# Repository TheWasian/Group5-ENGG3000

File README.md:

<div align="center">

# Whack-A-Mole · Wacker5

**Turn movement into gameplay with ultrasonic tracking and a 3D browser game.**

Three ESP32 boards. Six targets. One interactive engineering project.

[Overview](#overview) · [Gallery](#gallery) · [Getting started](#getting-started) · [Hardware](#hardware) · [Development](#development) · [Documentation](#documentation)

</div>

## Overview

Wacker5 brings a physical control system to the classic Whack-A-Mole game. Three ESP32-S3 boards use ultrasonic sensors to estimate a player's position, then send tracking data to a browser game where movement controls the hammer across six mole targets. You can also play with a mouse without connecting the hardware.

Built by **Group 5 for ENGG3000**, the project brings together embedded firmware, browser graphics, custom electronics, enclosure design, and sensor calibration. This repository contains the game, firmware, KiCad PCB designs, CAD models, and development records.

### Highlights

- **3D gameplay:** animated moles, a six-hole board, and five environments rendered with Three.js.
- **Arcade mechanics:** normal, golden, freeze, and bomb moles, with scores, lives, levels, and hit streaks.
- **Physical interaction:** three ultrasonic sensors track movement using two- or three-sensor position estimates.
- **Filtered tracking:** spike rejection and position smoothing; stale or held positions cannot score hits.
- **Live diagnostics:** the ESP32 hosts a dashboard showing sensor coverage, tracking, and target positions.
- **Local operation:** the game ships with its graphics bundle, and the hardware creates its own Wi-Fi network.
- **Hardware design files:** PCB schematics, board layouts, fabrication files, and printable enclosure models.

## Gallery

<table>
  <tr>
    <th>Physical prototype</th>
    <th>Current game interface</th>
  </tr>
  <tr>
    <td align="center"></td>
    <td align="center"></td>
  </tr>
</table>

The prototype photo shows the physical tracking setup. The current game screenshot shows the Sunny Garden environment, with 3D moles, six targets, and the score, lives, and hit-streak displays.

<details>
<summary><strong>View the custom PCB layout</strong></summary>

The PCB design and fabrication resources are in [ENGG3000-BaseStation](ENGG3000-BaseStation/).

</details>

## How it works

```mermaid
flowchart LR
    L[Left ultrasonic sensor] --> N1[ESP32 sensor node 1]
    C[Centre ultrasonic sensor] --> AP[ESP32 access point]
    R[Right ultrasonic sensor] --> N2[ESP32 sensor node 2]
    N1 <-->|ESP-NOW| AP
    N2 <-->|ESP-NOW| AP
    AP --> P[Position estimation and filtering]
    P --> API[Local HTTP API]
    API --> G[Browser game]
    API --> D[Live tracking dashboard]
```

The centre board coordinates range measurements and combines the readings into a position estimate. The browser maps valid, fresh positions into the game area and checks hits. When tracking briefly drops out, the last position may remain visible, but it cannot earn points.

The dashboard is hosted on the ESP32 at [192.168.4.1](http://192.168.4.1/). The game itself runs from the `UI-Code` folder on your computer.

## Getting started

### Play without hardware

1. Clone or download this repository. Extract the ZIP if downloading it.
2. Open `UI-Code/index.html` in a browser.
3. Select **Start Game**, then click the moles as they appear.

Keep the entire `UI-Code` folder together. The bundled game does not need Node.js, npm, or a development server to play. A WebGL 2 capable browser enables the 3D graphics; a CSS fallback is available if the renderer cannot start. Sound starts muted and can be enabled with the sound button.

### Play with the sensor system

1. Wire and upload the three board sketches using the [hardware setup guide](ESP-32%20Code/CHECKLIST.md).
2. Power the centre access point, followed by the left and right sensor nodes.
3. Connect your computer to **Wacker5** using the connection details in the setup guide.
4. Open the [tracking dashboard](http://192.168.4.1/) and confirm both nodes are online.
5. Open `UI-Code/index.html`, start the game, and move between the configured physical targets.

On Windows, you can run [GameLauncher.bat](GameLauncher.bat) to connect to Wacker5 and open the game. The launcher uses [Connect-Wacker5.ps1](Connect-Wacker5.ps1) to manage the Wi-Fi connection.

Keep the computer connected to Wacker5 while playing with sensors, and allow browser requests to the local controller if prompted. Sensor spacing, aiming, and target calibration are covered in the setup guide.

### Sensor cone visualisation and calibration

The [cones.html dashboard](ESP-32%20Code/Access_Point/cones.html) provides a live top-down view of the sensor setup. While connected to **Wacker5**, open [http://192.168.4.1/cones](http://192.168.4.1/cones) (the same dashboard is available at the controller's root address). The page is embedded in the access-point firmware, so there is no separate dashboard server to start.

- **Visualise coverage:** see each sensor's configured cone, overlapping coverage, measured echo arcs, player position, and the six game targets. Switch between the playing-area view and full sensor range to inspect alignment.
- **Check the setup:** use the live distances, sensor status, and aim angles to compare the physical layout with the firmware settings. The **Where to stand** table gives target positions in centimetres.
- **Try floor-position calibration:** stand at a chosen spot, select **Calibrate hole N**, and stay still through the countdown and capture. Repeat for the six holes, then walk between them to test detection with a 10, 15, or 20 cm test radius.

**Calibration on this page is a browser-only preview.** Saved positions stay in that browser's local storage; they do not change the ESP32 configuration or the game's hit zones. The cones represent the configured beam model, not measured detection boundaries. Recheck the physical setup and recalibrate after moving sensors. See the [calibration workflow](ESP-32%20Code/CHECKLIST.md#cone-page-hole-calibration-experiment) for details.

## Hardware

The tracking system uses **three ESP32-S3 boards with one ultrasonic sensor per board**.

The current layout has **30 cm between adjacent sensor references** (60 cm across the outer pair), with the centre sensor facing straight ahead and the side sensors angled **15.9° inward**. The [physical placement guide](ESP-32%20Code/CHECKLIST.md#physical-placement-spacing-and-angles) explains the reference points, screen distance, and housing setback.

| Component | Role | Firmware |
| --- | --- | --- |
| Centre ESP32-S3 + sensor | Wi-Fi access point, tracking, dashboard, and game API | [Access_Point](ESP-32%20Code/Access_Point/) |
| Left ESP32-S3 + sensor | Left-side range measurements | [Sensor_Node_1](ESP-32%20Code/Sensor_Node_1/) |
| Right ESP32-S3 + sensor | Right-side range measurements | [Sensor_Node_2](ESP-32%20Code/Sensor_Node_2/) |
| Computer with a browser | Game display and player interface | [UI-Code](UI-Code/) |
| Custom PCB and enclosures | Electronics integration and sensor mounting | [PCB files](ENGG3000-BaseStation/) · [CAD files](CAD/) |

Use the [setup guide](ESP-32%20Code/CHECKLIST.md) for pin assignments, sensor electrical requirements, firmware uploads, and physical alignment. The [bill of materials](Bill_of_materials.md) records the project's initial component cost estimate.

## Development

### Serve the game locally

For browser fixtures and development, run this from the repository root with Python 3:

```sh
python -m http.server 8000 --bind 127.0.0.1
```

Open the [game](http://127.0.0.1:8000/UI-Code/) or the [3D model gallery](http://127.0.0.1:8000/UI-Code/tests/three-preview.html). On systems where Python 3 is named `python3`, use that command instead.

### Build and check the game

With Node.js and npm installed:

```sh
cd UI-Code
npm ci
npm run build
npm run check:bundle
npm test
```

Rebuild after editing the 3D modules or vendored Three.js sources, and include the regenerated bundle with your changes. The checks cover models, bundle consistency, sound, and rendering performance logic. See the [3D development guide](UI-Code/3D-README.md) for browser previews and sensor-hit fixtures.

### Check tracking and backend logic

Run these from the repository root. The native suite needs Bash and a C++ compiler with AddressSanitizer and UndefinedBehaviorSanitizer support, such as a suitable Linux or WSL environment.

```sh
bash "ESP-32 Code/tests/run_native.sh"
node "ESP-32 Code/tests/game_backend_test.cjs"
node "ESP-32 Code/tests/hole_calibration_test.cjs"
```

Software checks complement physical testing: sensor accuracy and coverage must also be verified with the assembled hardware.

## Repository structure

| Path | Contents |
| --- | --- |
| [UI-Code/](UI-Code/) | Browser game, game services, 3D rendering, and frontend tests |
| [ESP-32 Code/](ESP-32%20Code/) | Access point and sensor firmware, tracking logic, dashboard, and tests |
| [ESP-32 Code/calibration/](ESP-32%20Code/calibration/) | Data-logging firmware, Python capture tools, and calibration results |
| [ENGG3000-BaseStation/](ENGG3000-BaseStation/) | KiCad project, component libraries, and fabrication outputs |
| [CAD/](CAD/) | Enclosure and hardware models in STL and GLB formats |
| [Blender/](Blender/) | Blender demonstration scene files |
| [WeeklyLogs/](WeeklyLogs/) | Sprint notes, progress screenshots, and testing records |

## Documentation

- [Hardware setup and troubleshooting](ESP-32%20Code/CHECKLIST.md)
- [3D game architecture and development](UI-Code/3D-README.md)
- [Sensor calibration and data collection](ESP-32%20Code/calibration/README.md)
- [Bill of materials](Bill_of_materials.md)
- [Project development logs](WeeklyLogs/)

## Contributing

Issues and pull requests are welcome. Describe the behaviour you want to change, include steps to reproduce bugs, and run the checks relevant to your changes. For hardware or tracking changes, include the board configuration, sensor arrangement, and physical test results where available.

## Team

Developed by ENGG3000 Group 5: **Alleluya Hamisi, Matthew Thompson, Fouad Ayoub, Cammilus John Baptist, and Shreenidhi Arunachalam**.

## License

This project is available under the [MIT License](LICENSE). Vendored Three.js retains its own [MIT license](UI-Code/vendor/three/LICENSE).

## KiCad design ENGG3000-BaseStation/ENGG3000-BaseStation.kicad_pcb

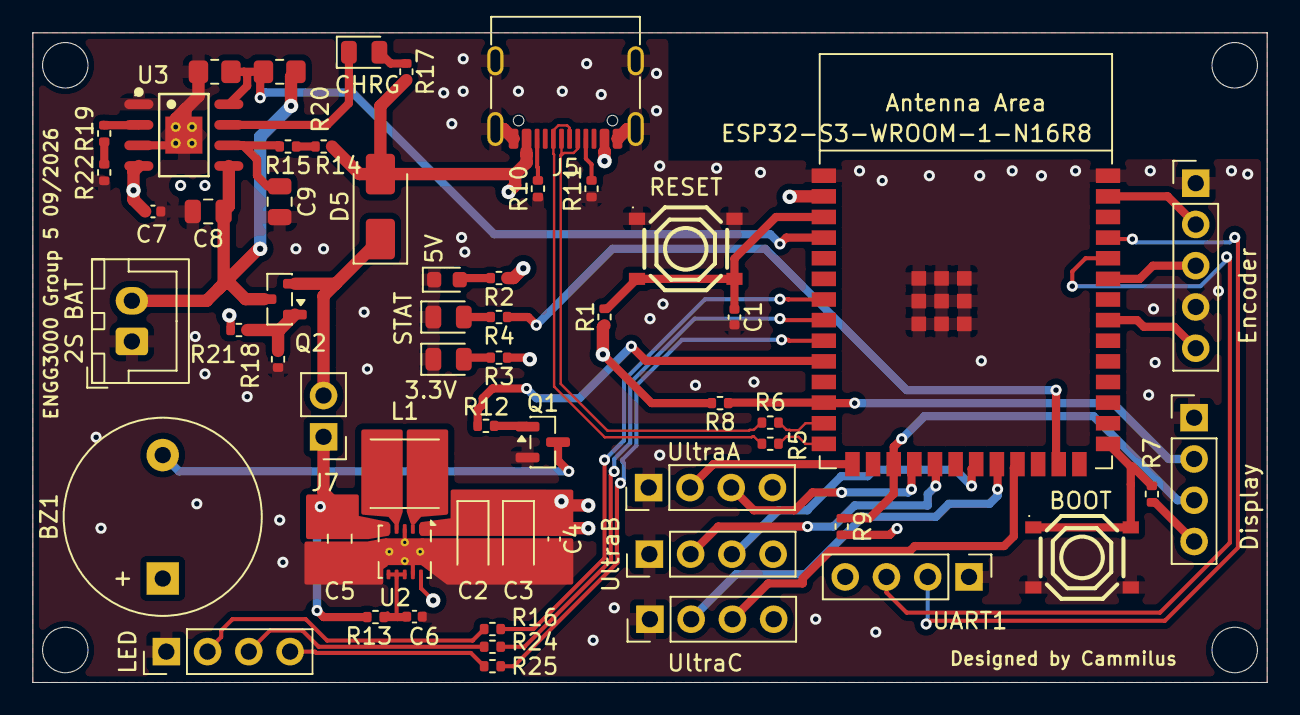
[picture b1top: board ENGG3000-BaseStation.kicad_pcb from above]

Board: 4 copper layers, 76.0 x 40.0 mm, 58 parts (0 on the bottom side), 51 nets.

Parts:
2S BAT: NiMH 2S Pack; JST_XH_B2B-XH-A_1x02_P2.50mm_Vertical
3.3V: 3.3V; LED_0805_2012Metric
5V: 5V; LED_0603_1608Metric
BOOT: BOOT; SW-SMD_4P-L5.1-W5.1-P3.70-LS6.5-TL_H1.5
BZ1: Buzzer; Buzzer_12x9.5RM7.6
C1, C4, C7: 1uF; C_0402_1005Metric
C2, C3: 10uF; CP_EIA-3216-18_Kemet-A
C5, C8, C9: 10uF; C_0805_2012Metric
C6: 100nF; C_0402_1005Metric
CHRG: CHRG; LED_0805_2012Metric
D5: SS14; D_SMA
Display: OLED; PinHeader_1x04_P2.54mm_Vertical
ESP32-S3-WROOM-1-N16R8: ESP32-S3-WROOM-1-N16R8; ESP32-S3-WROOM-1
Encoder: Encoder; PinHeader_1x05_P2.54mm_Vertical
J5: USB_C_Receptacle_USB2.0_16P; USB_C_Receptacle_G-Switch_GT-USB-7010ASV
J7: Power Switch; PinHeader_1x02_P2.54mm_Vertical
L1: 2.2uH; L_APV_ANR4020
LED: RGB LED; PinHeader_1x04_P2.54mm_Vertical
Q1: SS8050; SOT-23
Q2: AO3401A; SOT-23
R1, R2, R3, R4, R10, R11, R17: 5.1k; R_0402_1005Metric
R5, R6: 22; R_0402_1005Metric
R7, R8, R9, R18: 10k; R_0402_1005Metric
R12, R19, R21: 1k; R_0402_1005Metric
R13: 100R; R_0402_1005Metric
R14: 51k; R_0402_1005Metric
R15: 200k; R_0402_1005Metric
R16: 330R; R_0402_1005Metric
R20, R23: 10k; R_0805_2012Metric_Pad1.20x1.40mm_HandSolder
R22: 1.5k; R_0402_1005Metric
R24, R25: 220R; R_0402_1005Metric
RESET: RESET; SW-SMD_4P-L5.1-W5.1-P3.70-LS6.5-TL_H1.5
STAT: STATUS; LED_0805_2012Metric
U2: TPS63001DRCR; Texas_DRC0010J_ThermalVias
U3: CN3085; SOP-8_L4.9-W3.9-P1.27-LS6.0-BL-EP
UART1: UART0; PinHeader_1x04_P2.54mm_Vertical
UltraA: UltrasonicB; PinHeader_1x04_P2.54mm_Vertical
UltraB: UltrasonicA; PinHeader_1x04_P2.54mm_Vertical
UltraC: UltrasonicC; PinHeader_1x04_P2.54mm_Vertical

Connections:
+3.3V: BZ1.1 (+), C2.1, C3.1, C4.1, Display.4 (3.3V), ESP32-S3-WROOM-1-N16R8.2 (3V3), R1.1, R3.1, R7.2, R8.2, R9.2, U2.1 (VOUT), U2.10 (FB), UART1.4 (3.3V), UltraA.4 (3.3V), UltraB.4 (3.3V), UltraC.4 (3.3V)
+5V: C7.1, D5.2 (A), J5.A4 (VBUS), J5.A9 (VBUS), J5.B4 (VBUS), J5.B9 (VBUS), R2.1, R14.1, R17.2, R21.1, U3.4 (VIN)
/ESP_D+: ESP32-S3-WROOM-1-N16R8.14 (GPIO20/U1CTS/ADC2_CH9/CLK_OUT1/USB_D+), R5.1
/ESP_D-: ESP32-S3-WROOM-1-N16R8.13 (GPIO19/U1RTS/ADC2_CH8/CLK_OUT2/USB_D-), R6.1
BAT: 2S BAT.2 (+), C8.1, Q2.3 (D), R20.1, U3.5 (BAT)
D+: J5.A6 (D+), J5.B6 (D+), R5.2
D-: J5.A7 (D-), J5.B7 (D-), R6.2
FB: ESP32-S3-WROOM-1-N16R8.4 (GPIO4/TOUCH4/ADC1_CH3), R20.2, R23.1, U3.8 (FB)
GND: 2S BAT.1 (-), 3.3V.1 (K), 5V.1 (K), BOOT.2, C1.2, C2.2, C3.2, C4.2, C5.2, C6.2, C7.2, C8.2, C9.2, Display.1 (GND), ESP32-S3-WROOM-1-N16R8.1 (GND), ESP32-S3-WROOM-1-N16R8.40 (GND), ESP32-S3-WROOM-1-N16R8.41 (GND), Encoder.1 (GND), Encoder.4 (Button_C), J5.A1 (GND), J5.A12 (GND), J5.B1 (GND), J5.B12 (GND), J5.SH (SHIELD), LED.1 (GND), Q1.2 (E), R10.1, R11.1, R18.1, R22.2, R23.2, RESET.1, STAT.1 (K), U2.3 (PGND), U2.9 (GND), U2.11 (PGND), U3.1 (TEMP), U3.3 (GND), U3.9 (EP), UART1.1 (GND), UltraA.1 (GND), UltraB.1 (GND), UltraC.1 (GND)
GPIO1: ESP32-S3-WROOM-1-N16R8.39 (GPIO1/TOUCH1/ADC1_CH0), Encoder.2 (Button_A)
GPIO3: ESP32-S3-WROOM-1-N16R8.15 (GPIO3/TOUCH3/ADC1_CH2), UltraA.2 (TRIG)
GPIO7: ESP32-S3-WROOM-1-N16R8.7 (GPIO7/TOUCH7/ADC1_CH6), R16.2
GPIO10: ESP32-S3-WROOM-1-N16R8.18 (GPIO10/TOUCH10/ADC1_CH9/FSPICS0/FSPIIO4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), UltraA.3 (ECHO)
GPIO11: ESP32-S3-WROOM-1-N16R8.19 (GPIO11/TOUCH11/ADC2_CH0/FSPID/FSPIIO5/S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), UltraB.2 (TRIG)
GPIO13: ESP32-S3-WROOM-1-N16R8.21 (GPIO13/TOUCH13/ADC2_CH2/FSPIQ/FSPIIO7/S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), UltraB.3 (ECHO)
GPIO14: ESP32-S3-WROOM-1-N16R8.22 (GPIO14/TOUCH14/ADC2_CH3/FSPIWP/FSPIDQS/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), UltraC.2 (TRIG)
GPIO15: ESP32-S3-WROOM-1-N16R8.8 (GPIO15/U0RTS/ADC2_CH4/XTAL_32K_P), R24.1
GPIO16: ESP32-S3-WROOM-1-N16R8.9 (GPIO16/U0CTS/ADC2_CH5/XTAL_32K_N), R25.1
GPIO17: ESP32-S3-WROOM-1-N16R8.10 (GPIO17/U1TXD/ADC2_CH6), R12.1
GPIO21: ESP32-S3-WROOM-1-N16R8.23 (GPIO21), UltraC.3 (ECHO)
GPIO40: ESP32-S3-WROOM-1-N16R8.33 (MTDO/GPIO40/CLK_OUT2), Encoder.5 (Button_D)
GPIO43: ESP32-S3-WROOM-1-N16R8.35 (MTMS/GPIO42), Encoder.3 (Button_B)
GPIO48: ESP32-S3-WROOM-1-N16R8.25 (GPIO48/SPICLK_N/SUBSPICLK_N_DIFF), R4.1
unnamed: BZ1.2 (-), Q1.3 (C)
unnamed: 5V.2 (A), R2.2
unnamed: 3.3V.2 (A), R3.2
unnamed: R4.2, STAT.2 (A)
unnamed: CHRG.2 (A), R17.1
unnamed: CHRG.1 (K), U3.7 (~CHRG)
unnamed: D5.1 (K), J7.2 (+), Q2.2 (S)
unnamed: J5.A5 (CC1), R11.2
unnamed: J5.B5 (CC2), R10.2
unnamed: LED.4 (B), R25.2
unnamed: LED.3 (G), R24.2
unnamed: LED.2 (R), R16.1
unnamed: Q1.1 (B), R12.2
unnamed: Q2.1 (G), R18.2, R21.2
unnamed: R14.2, R15.1
unnamed: R19.2, R22.1
unnamed: C1.1, ESP32-S3-WROOM-1-N16R8.3 (EN), R1.2, RESET.2
unnamed: BOOT.1, ESP32-S3-WROOM-1-N16R8.27 (GPIO0/BOOT), R7.1
unnamed: ESP32-S3-WROOM-1-N16R8.36 (U0RXD/GPIO44/CLK_OUT2), UART1.3 (RXD)
unnamed: ESP32-S3-WROOM-1-N16R8.37 (U0TXD/GPIO43/CLK_OUT1), UART1.2 (TXD)
unnamed: C6.1, R13.1, U2.6 (EN), U2.7 (PS/SYNC), U2.8 (VINA)
unnamed: L1.2, U2.4 (L1)
unnamed: L1.1, U2.2 (L2)
unnamed: R19.1, U3.2 (ISET)
unnamed: C9.1, R15.2, U3.6 (RC)
SCL: Display.3 (RXD), ESP32-S3-WROOM-1-N16R8.17 (GPIO9/TOUCH9/ADC1_CH8/FSPIHD/SUBSPIHD), R9.1
SDA: Display.2 (TXD), ESP32-S3-WROOM-1-N16R8.12 (GPIO8/TOUCH8/ADC1_CH7/SUBSPICS1), R8.1
VIN: C5.1, J7.1 (-), R13.2, U2.5 (VIN)

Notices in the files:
README.md:
License: MIT
